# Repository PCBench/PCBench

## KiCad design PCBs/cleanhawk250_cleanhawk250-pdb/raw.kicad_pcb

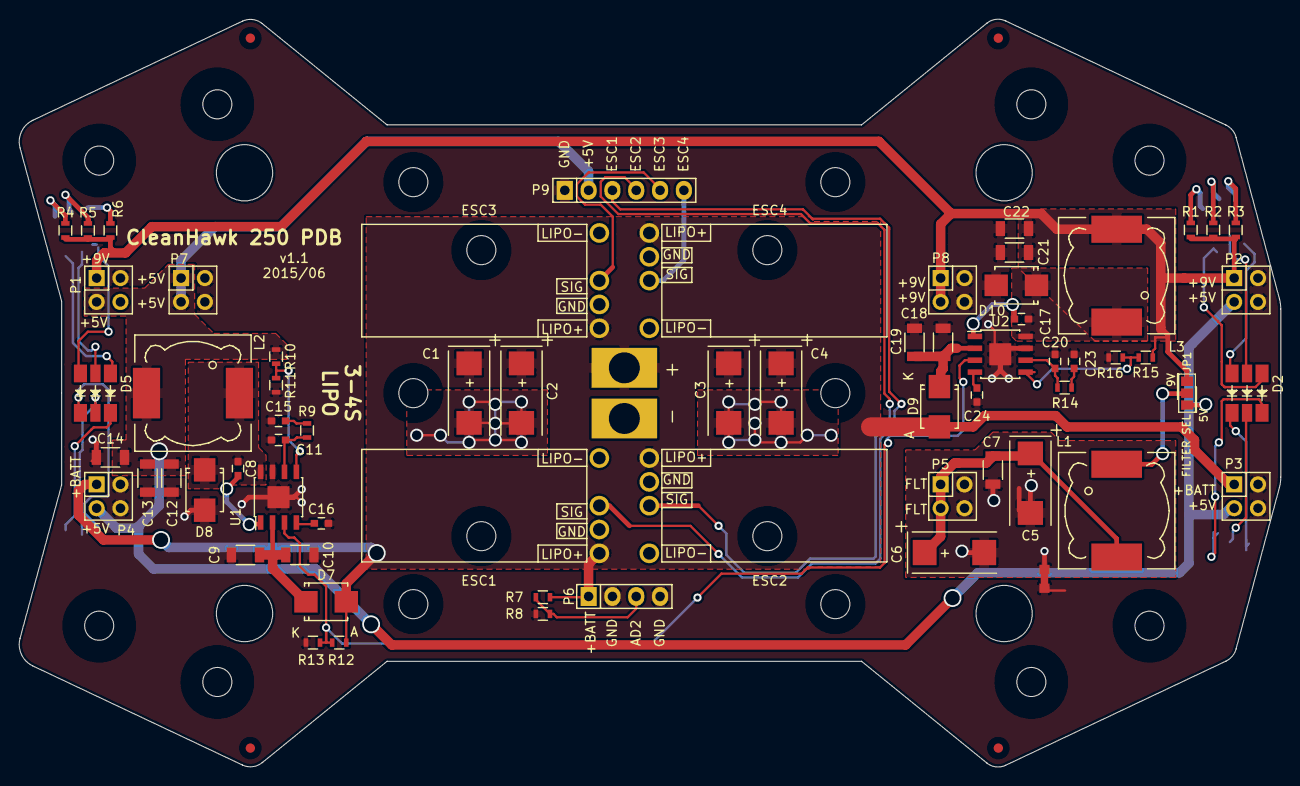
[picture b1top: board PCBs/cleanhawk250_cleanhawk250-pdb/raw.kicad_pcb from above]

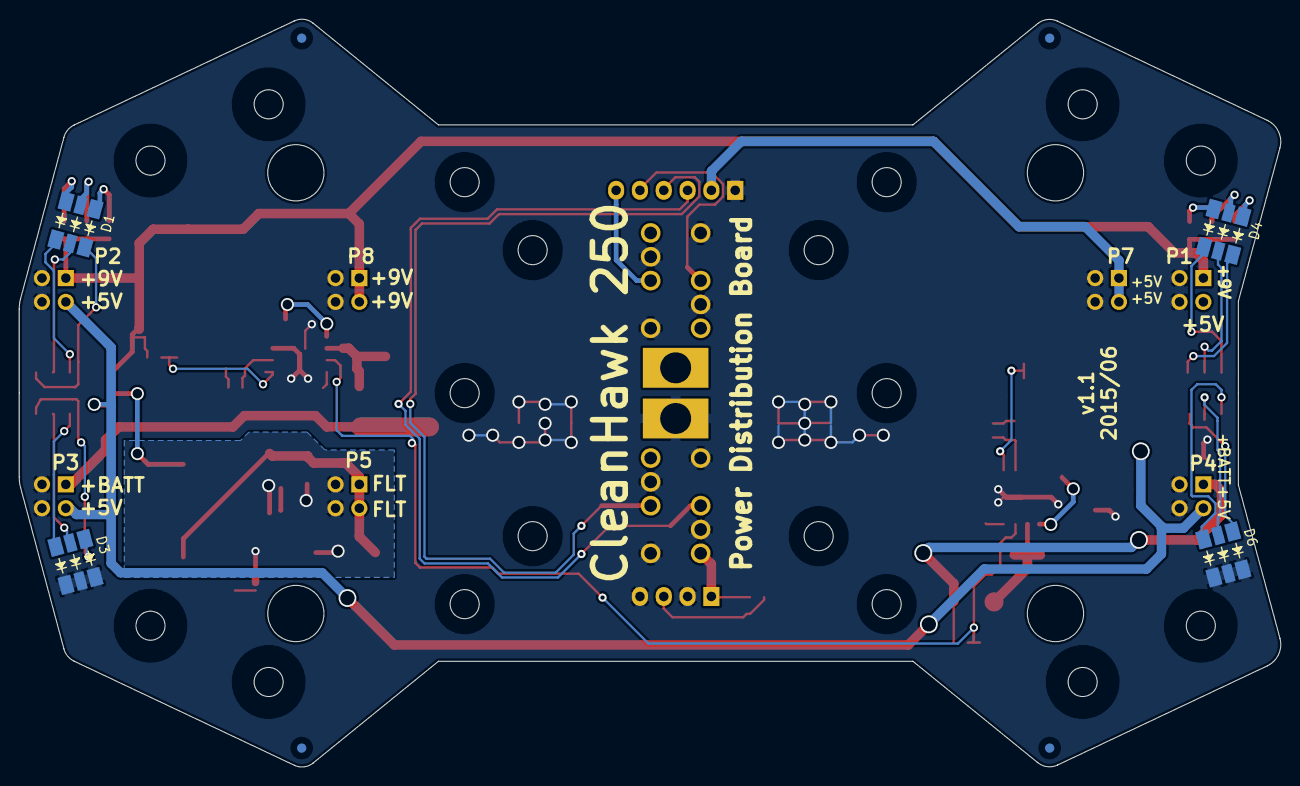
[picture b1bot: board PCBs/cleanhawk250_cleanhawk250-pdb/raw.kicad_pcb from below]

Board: 2 copper layers, 134.5 x 79.7 mm, 80 parts (8 on the bottom side), 45 nets.

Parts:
C1, C2, C3, C4: 33uF/25V/np; TantalC_SizeD_EIA-7343_Reflow
C5, C6: 100uF/16V; TantalC_SizeD_EIA-7343_Reflow
C7, C9, C10, C18, C19: 10uF/35V; C_1206
C8, C17: 100nF; C_0603
C11, C20: 18pF; C_0603
C12, C13, C14: 22uF/10V; C_1206
C15, C23: 680pF; C_0603
C16, C24: 8.2nF; C_0603
C21, C22: 22uF/16V; C_1206
D1, D2, D3, D4, D5, D6: RGB_LED_5050; LED_5050_RGB
D7, D8, D9, D10: B340LB; Diode-SMB_Standard
ESC1, ESC2, ESC3, ESC4: KISS_ESC_18A; Kiss_ESC_18A_v1.1
F1, F2, F3, F4, F5, F6, F7, F8: SPECIAL; FIDUCIAL_1MM
FRAME1: SPECIAL; Emax250_Bottom_Holes
JP1: FILTER SEL; AB2_SJMP_03-1
JP2: JUMPER; NetTie-I_Connected_SMD
L1: 820uH; Choke_SMD_12x12mm_h6mm
L2, L3: 8.2uH; Choke_SMD_12x12mm_h6mm
P1, P2, P3, P4, P5, P7, P8: CONN_02X02; Pin_Header_Straight_2x02
P6: CONN_01X04; Pin_Header_Straight_1x04
P9: CONN_01X06; Pin_Header_Straight_1x06
R1, R3: 68; R_0603
R2, R5: 120; R_0603
R4, R6: 68/np; R_0603
R7, R10, R15: 10k/1%; R_0603
R8: 2.32k/1%; R_0603
R9, R14: 78.7k; R_0603
R11: 1.91k/1%; R_0603
R12: 169k/np; R_0603
R13: 28k/np; R_0603
R16: 976/1%; R_0603
U1, U2: TPS54331; SOIC-8-1EP_3.9x4.9mm_Pitch1.27mm
W1: WIREPADS; WirePads_12AWG_TH

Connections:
+5V: C12.1, C13.1, C14.1, JP1.3, L2.2, P1.3, P2.3, P3.3, P4.3, P7.1, P7.3, P9.2, R10.1
+9V: C21.1, C22.1, JP1.1, L3.2, P1.1, P2.1, P8.1, P8.3, R1.2, R2.2, R3.2, R4.2, R5.2, R6.2, R15.1
+BATT: C1.1, C2.1, C3.1, C4.1, D7.2, D9.2, ESC1.1, ESC2.1, ESC3.1, ESC4.1, P3.1, P4.1, P6.1, R7.2, R12.1, W1.+
ESC1: ESC1.2, P9.3
ESC2: ESC2.2, P9.4
ESC3: ESC3.2, P9.5
ESC4: ESC4.2, P9.6
GND: C1.2, C2.2, C3.2, C4.2, C9.2, C10.2, C11.2, C12.2, C13.2, C14.2, C15.2, C16.2, C18.2, C19.2, C20.2, C21.2, C22.2, C23.2, C24.2, D3.4, D3.5, D3.6, D6.4, D6.5, D6.6, D8.2, D10.2, ESC1.3, ESC1.4, ESC2.3, ESC2.4, ESC3.3, ESC3.4, ESC4.3, ESC4.4, JP2.1, P1.2, P1.4, P2.2, P2.4, P3.2, P3.4, P4.2, P4.4, P6.2, P6.4, P7.2, P7.4, P8.2, P8.4, P9.1, R8.2, R11.2, R13.2, R16.2, U1.7, U1.9, U2.7, U2.9, W1.-
GNDA: C5.2, C6.2, C7.2, JP2.2, P5.2, P5.4
unnamed: C5.1, C6.1, C7.1, L1.2, P5.1, P5.3
unnamed: C8.1, U1.1
unnamed: C8.2, D8.1, L2.1, U1.8
unnamed: C9.1, C10.1, D7.1, U1.2
unnamed: C11.1, R9.1, U1.6
unnamed: C15.1, R9.2
unnamed: C16.1, U1.4
unnamed: C17.1, U2.1
unnamed: C17.2, D10.1, L3.1, U2.8
unnamed: C18.1, C19.1, D9.1, U2.2
unnamed: C20.1, R14.1, U2.6
unnamed: C23.1, R14.2
unnamed: C24.1, U2.4
unnamed: D1.1, R1.1
unnamed: D1.2, R2.1
unnamed: D1.3, R3.1
unnamed: D1.4, D2.3
unnamed: D1.5, D2.2
unnamed: D1.6, D2.1
unnamed: D2.4, D3.3
unnamed: D2.5, D3.2
unnamed: D2.6, D3.1
unnamed: D4.1, R4.1
unnamed: D4.2, R5.1
unnamed: D4.3, R6.1
unnamed: D4.4, D5.3
unnamed: D4.5, D5.2
unnamed: D4.6, D5.1
unnamed: D5.4, D6.3
unnamed: D5.5, D6.2
unnamed: D5.6, D6.1
unnamed: JP1.2, L1.1
unnamed: P6.3, R7.1, R8.1
unnamed: R10.2, R11.1, U1.5
unnamed: R15.2, R16.1, U2.5
REG_EN: R12.2, R13.1, U1.3, U2.3

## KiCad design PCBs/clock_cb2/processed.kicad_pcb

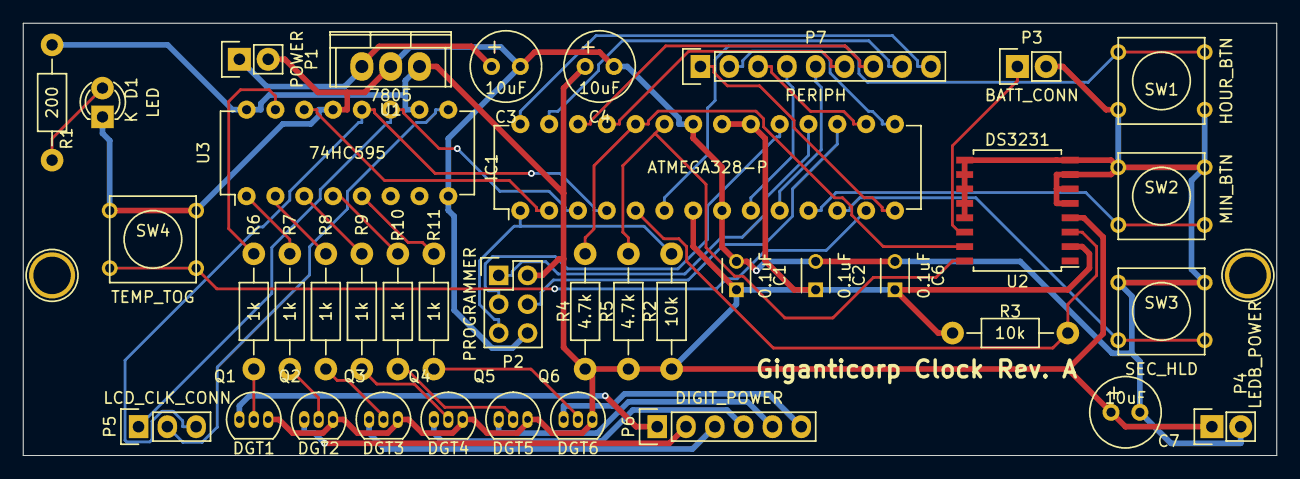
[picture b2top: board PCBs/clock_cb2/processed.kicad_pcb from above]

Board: 2 copper layers, 110.5 x 38.1 mm, 41 parts (0 on the bottom side), 47 nets.

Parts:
C1, C2, C6: 0.1uF; C_Disc_D3_P2.5
C3, C4, C7: 10uF; Elko_vert_11.2x6.3mm_RM2.5
D1: LED; LED-3MM
IC1: ATMEGA328-P; DIP-28_W7.62mm
P1: POWER; Pin_Header_Straight_1x02
P2: PROGRAMMER; Pin_Header_Straight_2x03
P3: BATT_CONN; Pin_Header_Straight_1x02
P4: LEDB_POWER; Pin_Header_Straight_1x02
P5: LCD_CLK_CONN; Pin_Header_Straight_1x03
P6: DIGIT_POWER; Pin_Header_Straight_1x06
P7: PERIPH; Pin_Header_Straight_1x09
Q1: DGT1; TO-92_Inline_Narrow_Oval
Q2: DGT2; TO-92_Inline_Narrow_Oval
Q3: DGT3; TO-92_Inline_Narrow_Oval
Q4: DGT4; TO-92_Inline_Narrow_Oval
Q5: DGT5; TO-92_Inline_Narrow_Oval
Q6: DGT6; TO-92_Inline_Narrow_Oval
R1: 200; Resistor_Horizontal_RM10mm
R2, R3: 10k; Resistor_Horizontal_RM10mm
R4, R5: 4.7k; Resistor_Horizontal_RM10mm
R6, R7, R8, R9, R10, R11: 1k; Resistor_Horizontal_RM10mm
REF1, REF2: 1pin
SW1: HOUR_BTN; SW_PUSH_SMALL
SW2: MIN_BTN; SW_PUSH_SMALL
SW3: SEC_HLD; SW_PUSH_SMALL
SW4: TEMP_TOG; SW_PUSH_SMALL
U1: 7805; TO-220
U2: DS3231; SOIC-16_7.5x10.3mm_Pitch1.27mm
U3: 74HC595; DIP-16_W7.62mm

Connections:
/DIG1: P6.1, Q1.1
/DIG2: P6.2, Q2.1
/DIG3: P6.3, Q3.1
/DIG4: P6.4, Q4.1
/DIG5: P6.5, Q5.1
/DIG6: P6.6, Q6.1
CLK: IC1.3, P5.1, U3.11
I2C_CLK: IC1.23, R5.2, U2.16
I2C_DATA: IC1.24, R4.2, U2.15
unnamed: C3.1, P1.1, U1.1
unnamed: D1.2, R1.1
unnamed: IC1.2, U3.14
unnamed: IC1.5, R3.1, U2.3
unnamed: IC1.6, SW1.2
unnamed: IC1.9, P7.4
unnamed: IC1.10, P7.5
unnamed: IC1.11, SW2.2
unnamed: IC1.12, SW3.2
unnamed: IC1.13, SW4.2
unnamed: IC1.14, P7.1
unnamed: IC1.15, P7.2
unnamed: IC1.16, P7.3
unnamed: IC1.25, P7.6
unnamed: IC1.26, P7.7
unnamed: IC1.27, P7.8
unnamed: IC1.28, P7.9
unnamed: P3.1, U2.14
unnamed: P5.2, U3.9
unnamed: Q1.2, R6.1
unnamed: Q2.2, R7.1
unnamed: Q3.2, R8.1
unnamed: Q4.2, R9.1
unnamed: Q5.2, R10.1
unnamed: Q6.2, R11.1
unnamed: R6.2, U3.15
unnamed: R7.2, U3.1
unnamed: R8.2, U3.2
unnamed: R9.2, U3.3
unnamed: R10.2, U3.4
unnamed: R11.2, U3.5
PROG_GND: C1.2, C2.2, C3.2, C4.2, C6.2, C7.2, D1.1, IC1.8, IC1.22, P1.2, P2.6, P3.2, P4.2, SW1.1, SW2.1, SW3.1, SW4.1, U1.2, U2.5, U2.6, U2.7, U2.8, U2.9, U2.10, U2.11, U2.12, U2.13, U3.8, U3.13
PROG_MISO: IC1.18, P2.1
PROG_MOSI: IC1.17, P2.4
PROG_RESET: IC1.1, P2.5, R2.2
PROG_SCK: IC1.19, P2.3
PROG_VCC: C1.1, C2.1, C4.1, C6.1, C7.1, IC1.7, IC1.20, IC1.21, P2.2, P4.1, Q1.3, Q2.3, Q3.3, Q4.3, Q5.3, Q6.3, R1.2, R2.1, R3.2, R4.1, R5.1, U1.3, U2.2, U2.4, U3.10, U3.16
SDL: IC1.4, P5.3, U3.12

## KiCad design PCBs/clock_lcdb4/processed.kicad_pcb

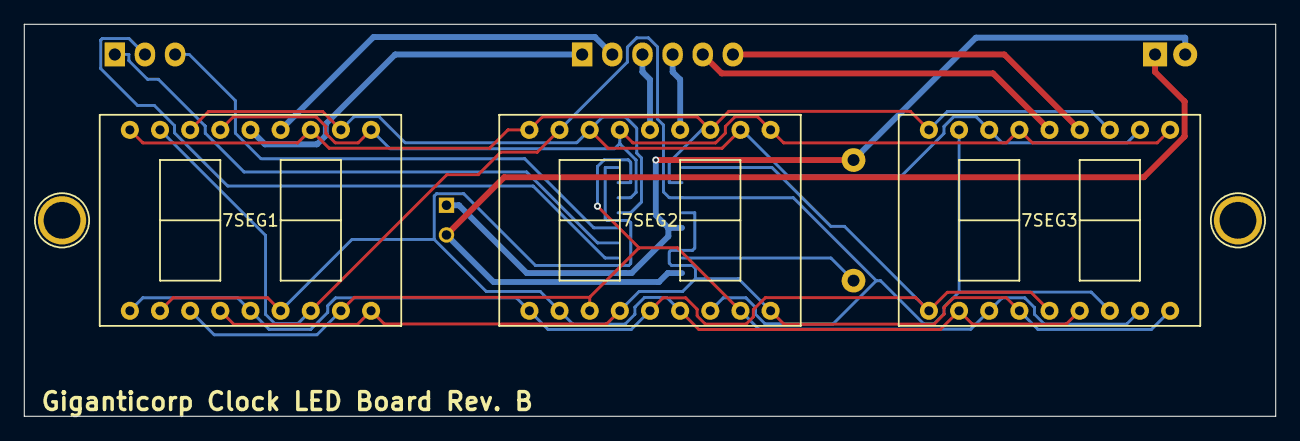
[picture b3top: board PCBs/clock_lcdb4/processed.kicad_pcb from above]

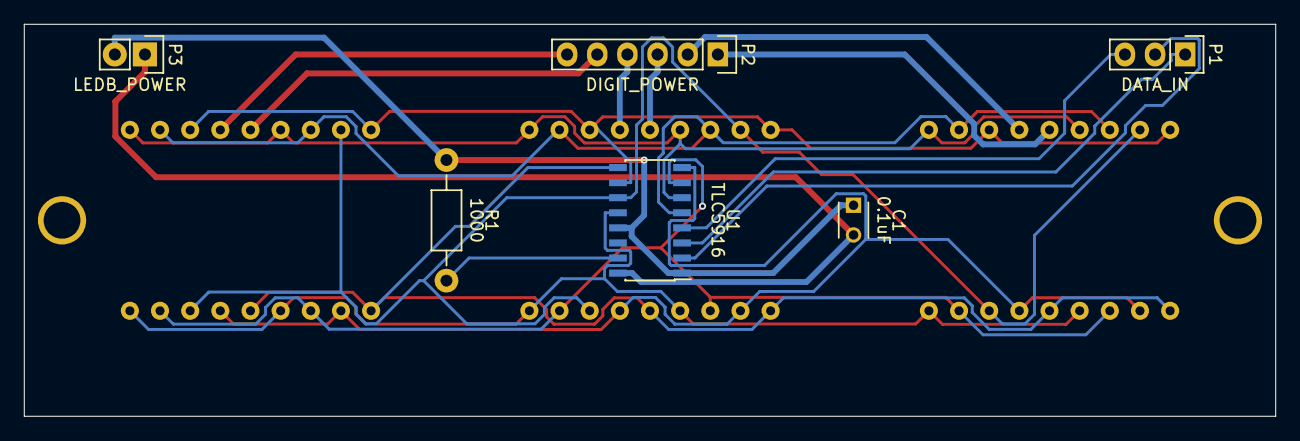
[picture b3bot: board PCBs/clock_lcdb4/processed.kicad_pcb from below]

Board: 2 copper layers, 105.4 x 33.0 mm, 11 parts (6 on the bottom side), 20 nets.

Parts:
7SEG1, 7SEG2, 7SEG3: LTD-5621AG
C1: 0.1uF; C_Disc_D3_P2.5
P1: DATA_IN; Pin_Header_Straight_1x03
P2: DIGIT_POWER; Pin_Header_Straight_1x06
P3: LEDB_POWER; Pin_Header_Straight_1x02
R1: 1000; Resistor_Horizontal_RM10mm
REF1, REF2: 1pin
U1: TLC5916; SOIC-16_3.9x9.9mm_Pitch1.27mm

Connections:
CLK: P1.1, U1.3
DIG1: 7SEG1.14, P2.1
DIG2: 7SEG1.13, P2.2
DIG3: 7SEG2.14, P2.3
DIG4: 7SEG2.13, P2.4
DIG5: 7SEG3.14, P2.5
DIG6: 7SEG3.13, P2.6
GND: C1.1, P3.2, R1.1, U1.1, U1.13
unnamed: R1.2, U1.15
SDA: P1.2, U1.2
SDL: P1.3, U1.4
SEGA: 7SEG1.11, 7SEG1.16, 7SEG2.11, 7SEG2.16, 7SEG3.11, 7SEG3.16, U1.5
SEGB: 7SEG1.10, 7SEG1.15, 7SEG2.10, 7SEG2.15, 7SEG3.10, 7SEG3.15, U1.6
SEGC: 7SEG1.3, 7SEG1.8, 7SEG2.3, 7SEG2.8, 7SEG3.3, 7SEG3.8, U1.7
SEGD: 7SEG1.2, 7SEG1.6, 7SEG2.2, 7SEG2.6, 7SEG3.2, 7SEG3.6, U1.8
SEGDP: 7SEG1.4, 7SEG1.9, 7SEG2.4, 7SEG2.9, 7SEG3.4, 7SEG3.9, U1.12
SEGE: 7SEG1.1, 7SEG1.5, 7SEG2.1, 7SEG2.5, 7SEG3.1, 7SEG3.5, U1.9
SEGF: 7SEG1.12, 7SEG1.18, 7SEG2.12, 7SEG2.18, 7SEG3.12, 7SEG3.18, U1.10
SEGG: 7SEG1.7, 7SEG1.17, 7SEG2.7, 7SEG2.17, 7SEG3.7, 7SEG3.17, U1.11
VDD: C1.2, P3.1, U1.16

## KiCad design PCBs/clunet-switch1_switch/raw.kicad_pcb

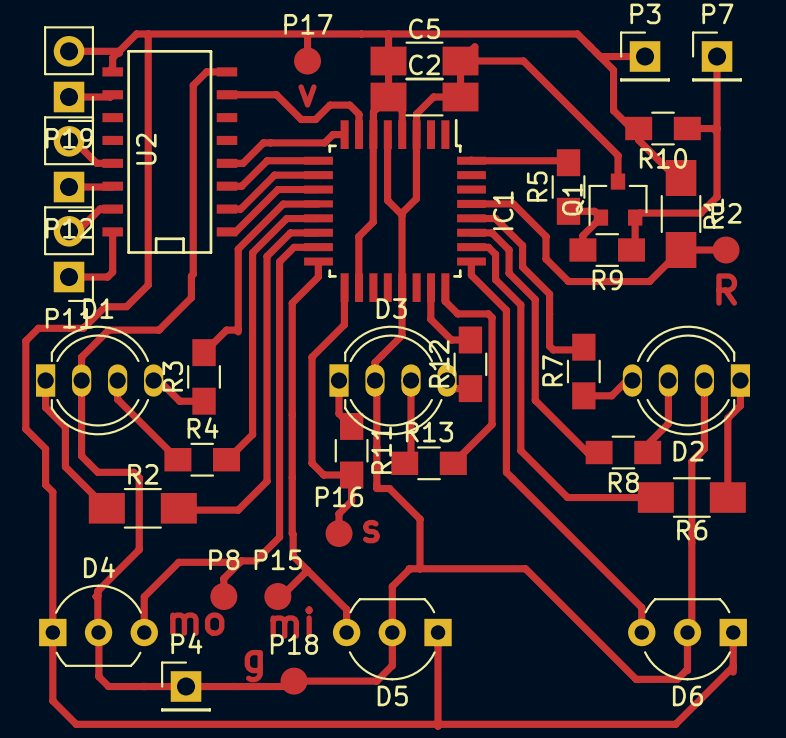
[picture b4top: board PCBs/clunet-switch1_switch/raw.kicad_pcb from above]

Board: 2 copper layers, 36 parts (0 on the bottom side), 37 nets.

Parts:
C2: 10mkf; C_1206_HandSoldering
C5: C_Small; C_1206_HandSoldering
D1, D2, D3: Led1; LED_D5.0mm-4-LL
D4, D5, D6: AH201; TO-92_Inline_Wide
IC1: ATMEGA8A-A; TQFP-32_7x7mm_Pitch0.8mm-LUT
P2: Reset; Measurement_Point_Round-SMD-Pad_Small
P3: Vcc; Socket_Strip_Straight_1x01_Pitch2.54mm
P4: Gnd; Socket_Strip_Straight_1x01_Pitch2.54mm
P7: Clunet; Socket_Strip_Straight_1x01_Pitch2.54mm
P8: CON_MOS; Measurement_Point_Round-SMD-Pad_Small
P11: R1_; Socket_Strip_Straight_1x02_Pitch2.54mm
P12: R2_; Socket_Strip_Straight_1x02_Pitch2.54mm
P15: CON_MIS; Measurement_Point_Round-SMD-Pad_Small
P16: CON_SCK; Measurement_Point_Round-SMD-Pad_Small
P17: Vcc_Prog; Measurement_Point_Round-SMD-Pad_Small
P18: Gnd_Prog; Measurement_Point_Round-SMD-Pad_Small
P19: SPK; Socket_Strip_Straight_1x02_Pitch2.54mm
Q1: PNP BC858; SOT-23
R1: 1.5K; R_1206_HandSoldering
R2, R6: 470R; R_1206_HandSoldering
R3, R4, R7, R8, R11, R12, R13: 470R; R_0805_HandSoldering
R5: 2.2K; R_0805_HandSoldering
R9: 22K; R_0805_HandSoldering
R10: 560R; R_0805_HandSoldering
U2: ULN2003-norm; SO-16-N

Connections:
/LED1_1: IC1.14, R2.2
/LED1_2: IC1.13, R4.2
/LED1_3: IC1.12, R3.2
/LED2_1: IC1.17, P16.1, R11.2
/LED2_2: IC1.23, R12.2
/LED2_3: IC1.24, R13.2
/LED3_1: IC1.26, R6.2
/LED3_2: IC1.27, R8.2
/LED3_3: IC1.28, R7.2
/R1_1: IC1.11, U2.1
/R1_2: IC1.10, U2.2
/R2_1: IC1.9, U2.3
/R2_2: IC1.8, U2.4
/SW1: D4.3, IC1.15, P8.1
/SW2: D5.3, IC1.16, P15.1
/SW3: D6.3, IC1.25
/spk: IC1.7, U2.7
GND: C2.2, C5.2, D1.2, D2.2, D3.2, D4.2, D5.2, D6.2, IC1.3, IC1.5, IC1.21, P4.1, P18.1, Q1.3, U2.8
unnamed: D1.1, R2.1
unnamed: D1.3, R4.1
unnamed: D1.4, R3.1
unnamed: D2.1, R6.1
unnamed: D2.3, R8.1
unnamed: D2.4, R7.1
unnamed: D3.1, R11.1
unnamed: D3.3, R13.1
unnamed: D3.4, R12.1
unnamed: IC1.29, P2.1, R1.2
unnamed: IC1.32, R5.2
unnamed: P11.1, U2.16
unnamed: P11.2, U2.15
unnamed: P12.1, U2.14
unnamed: P12.2, U2.13
unnamed: P19.1, U2.10
unnamed: Q1.1, R5.1, R9.2
VCC: C2.1, C5.1, D4.1, D5.1, D6.1, IC1.4, IC1.6, IC1.18, P3.1, P17.1, P19.2, R1.1, R10.2, U2.9
clunet: P7.1, Q1.2, R9.1, R10.1

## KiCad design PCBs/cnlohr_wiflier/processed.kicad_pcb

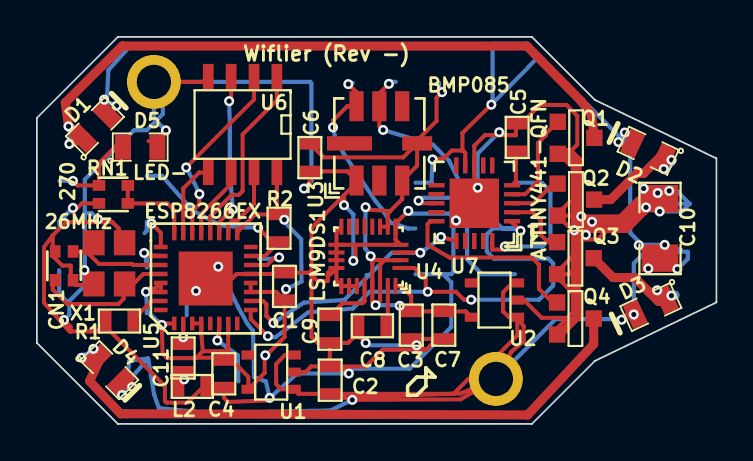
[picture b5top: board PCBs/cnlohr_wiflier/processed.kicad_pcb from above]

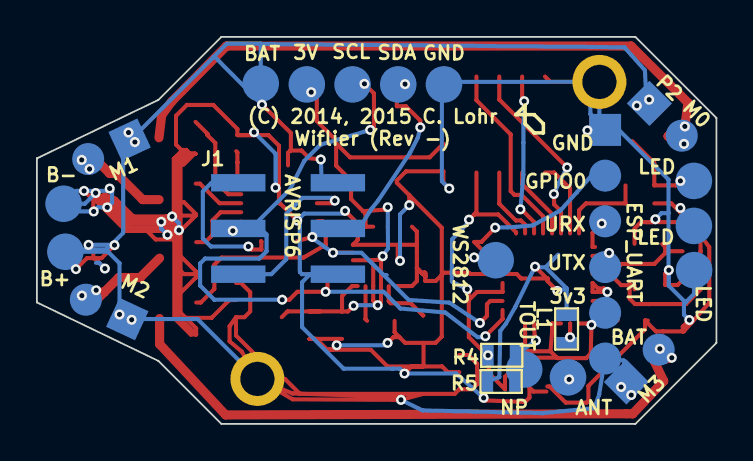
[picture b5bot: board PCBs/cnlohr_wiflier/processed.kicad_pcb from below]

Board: 2 copper layers, 37.8 x 21.5 mm, 57 parts (22 on the bottom side), 38 nets.

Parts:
C1, C2, C3: 10uF; SM0603
C4: 1uF; SM0603
C5: 1u; SM0603
C6, C7, C8: .1u; SM0603
C9: 10nF; SM0603
C10: 100uF; SM1206
C11: 5.6pF; SM0603
CN1: 10p; NETWORK0606
D1, D2, D3, D4: 20V_500mA; SM0805
D5: LED-; SM0805
J1: AVRISP6; RIBBON6SMT
L1, L2: NP; SM0603
P1: WS2812; .1SMTPIN
P2: M0; SMT_1x2
P3: M1; SMT_1x2
P4: M2; SMT_1x2
P5: M3; SMT_1x2
P6: ANT; .1SMTPIN
P7, P8: HOLE-1.9MM
P9: SDA; .1SMTPIN
P10: SCL; .1SMTPIN
P11: 3V; .1SMTPIN
P12: GND; .1SMTPIN
P13, P14, P15: LED; .1SMTPIN
P16: BAT; .1SMTPIN
P17: TOUT; .1SMTPIN
P21: B+; .1SMTPIN
P24: B-; .1SMTPIN
P32: ESP_UART; SMT_1x6
Q1, Q2, Q3, Q4: 7A_20V; SOT23GDS
R1, R2, R4: 12k; SM0603
R5: NP; SM0603
RN1: 270; NETWORK0606
U1, U2: MCP1824/3.0; SOT23-5
U3: BMP085
U4: LSM9DS1; LGA-24B
U5: ESP8266EX; QFN32
U6: W25Q80DV; SO8E
U7: ATTINY441-QFN; QFN20
X1: 26MHz; XTAL4P

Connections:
+3.3V: C1.1, C4.1, P32.5, R2.2, R4.1, U1.5, U5.1, U5.3, U5.4, U5.7, U5.11, U5.12, U5.17, U5.29, U5.30, U6.8
+3.3VP: C3.1, C6.2, C7.1, P11.1, U2.5, U3.3, U3.4, U4.1, U4.3, U4.7, U4.8, U4.22, U4.23
+BATT: C2.1, C10.1, D1.2, D2.2, D3.2, D4.2, J1.2, P2.1, P3.1, P4.1, P5.1, P8.1, P16.1, P21.1, P32.6, U1.1, U1.3, U2.1, U2.3, U7.9
AVRMISO: J1.1, U7.20
AVRRST: J1.5, U7.13
GND: C1.2, C2.2, C3.2, C4.2, C5.1, C6.1, C7.2, C8.1, C9.1, C10.2, CN1.2, CN1.3, D5.2, J1.6, L1.2, L2.2, P7.1, P12.1, P15.1, P24.1, P32.1, Q1.S, Q2.S, Q3.S, Q4.S, R1.1, R5.2, U1.2, U2.2, U3.1, U4.5, U4.6, U4.13, U4.14, U4.15, U4.16, U4.17, U4.18, U4.19, U4.20, U5.13, U5.33, U6.4, U7.8, U7.21, X1.3, X1.4
GP5: RN1.1, RN1.3, U5.24
GPIO0: P32.2, R2.1, U5.15
GPIO2: P1.1, U5.14
M0P: D1.1, P2.2, Q1.D
M1P: D2.1, P3.2, Q2.D
M2P: D3.1, P4.2, Q3.D
M3P: D4.1, P5.2, Q4.D
MTR0: Q1.G, U7.4
MTR1: Q2.G, U7.3
MTR2: Q3.G, U7.2
MTR3: Q4.G, U7.15
unnamed: C11.1, L1.1, U5.2
unnamed: C11.2, L2.1, P6.1
unnamed: CN1.1, U5.28, X1.2
unnamed: R1.2, U5.31
unnamed: CN1.4, U5.27, X1.1
unnamed: C8.2, U4.24
unnamed: C9.2, U4.21
unnamed: P13.1, RN1.2
unnamed: D5.1, P14.1, RN1.4
unnamed: C5.2, U7.5
unnamed: U5.22, U6.2
unnamed: U5.23, U6.5
unnamed: U5.19, U6.3
unnamed: U5.18, U6.7
unnamed: U5.20, U6.1
unnamed: U5.21, U6.6
SCL: J1.3, P10.1, U3.6, U4.2, U5.9, U7.1
SDA: J1.4, P9.1, U3.7, U4.4, U5.10, U7.16
TOUT: P17.1, R4.2, R5.1, U5.6
URX: P32.3, U5.25
UTX: P32.4, U5.26

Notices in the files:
PCBs/cnlohr_wiflier/processed.kicad_pcb:
(C) 2014, 2015 C. Lohr
